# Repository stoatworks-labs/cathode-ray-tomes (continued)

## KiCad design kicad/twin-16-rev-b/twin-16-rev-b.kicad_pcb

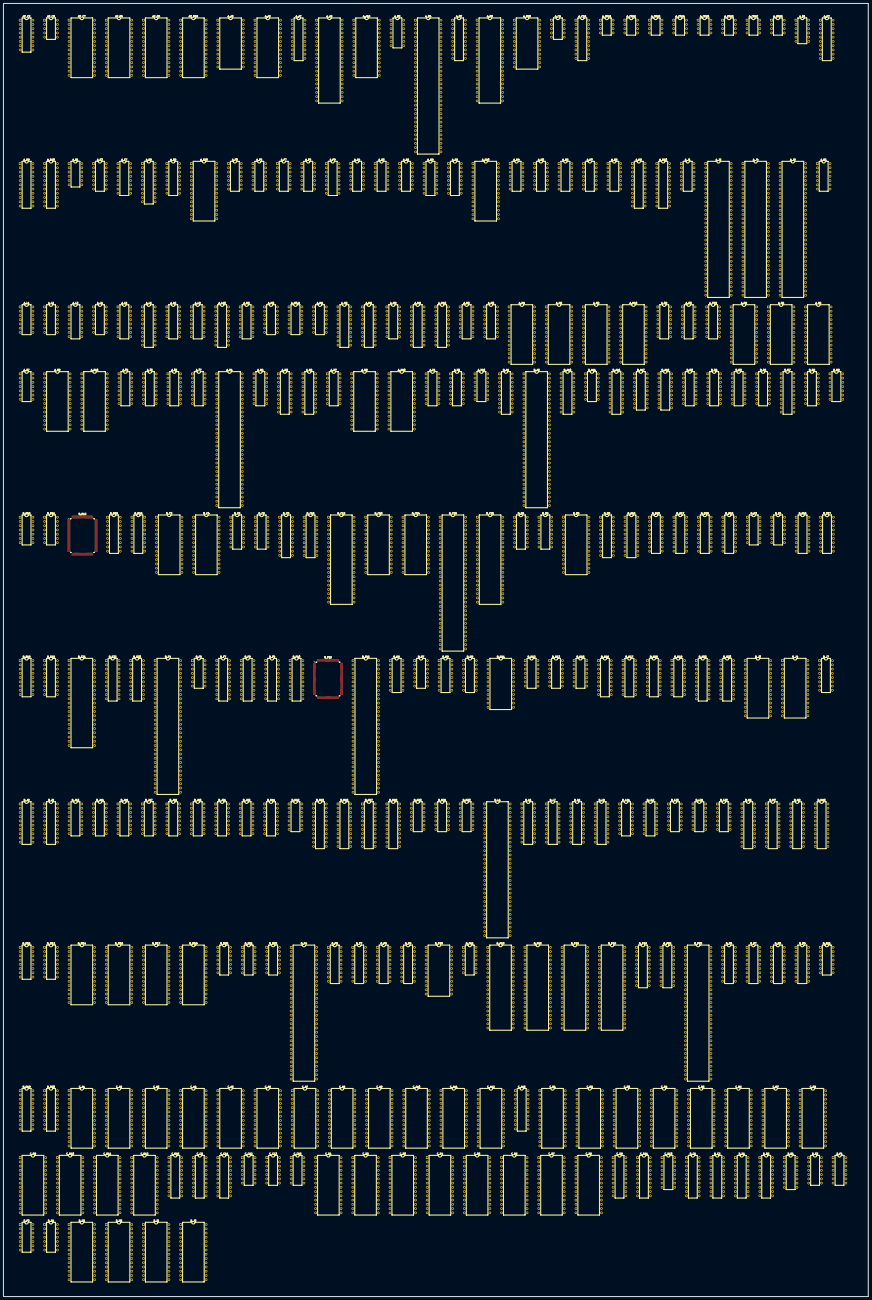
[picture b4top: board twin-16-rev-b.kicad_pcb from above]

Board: 2 copper layers, 517.2 x 773.3 mm, 297 parts (0 on the bottom side), 1272 nets, no tracks yet.

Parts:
AP_C2: YM3012; DIP-16_W7.62mm
AP_C5: 007340; DIP-10_W7.62mm
AP_C7: 23C1000; DIP-28_W15.24mm
AP_R4, AP_R6, AP_R10: 27C512; DIP-28_W15.24mm
A_A3: YM2151; DIP-24_W15.24mm
A_A5: 23C1000; DIP-28_W15.24mm
A_A7: 74LS273; DIP-20_W7.62mm
A_A8: Z80CPU; DIP-40_W15.24mm
A_A10: 27C256; DIP-28_W15.24mm
A_B2: uPC324; DIP-14_W7.62mm
A_B4: 007232; DIP-64_W15.24mm
A_B7: 74LS273; DIP-20_W7.62mm
A_B8: μPD7759; DIP-40_W15.24mm
A_B10: 2128SL; DIP-24_W15.24mm
A_C4: 007340; DIP-10_W7.62mm
A_C10: 74LS374; DIP-20_W7.62mm
A_CRA1, A_CRA2, A_CRA3, A_CRA4, A_CRA5, A_CRA6, A_CRA7, A_CRA8: 005273; DIP-8_W7.62mm
A_D1: MB3722; DIP-12_W7.62mm
A_D7: 74LS273; DIP-20_W7.62mm
A_D9, A_D10: 007644; DIP-22_W7.62mm
A_E1: 005924; DIP-12_W7.62mm
A_E3: uPC324; DIP-14_W7.62mm
A_E7: 74LS138; DIP-16_W7.62mm
A_E8: PAL16L8’; DIP-20_W7.62mm
A_E9: 74LS157; DIP-16_W7.62mm
A_E10: 6264SL; DIP-28_W15.24mm
A_F3: uPC324; DIP-14_W7.62mm
A_F6, A_F8: 74LS74; DIP-14_W7.62mm
A_F7: 74LS04; DIP-14_W7.62mm
A_F9: 74LS157; DIP-16_W7.62mm
A_G4: uPC324; DIP-14_W7.62mm
A_G5: 74LS74; DIP-14_W7.62mm
A_G6: 74LS00; DIP-14_W7.62mm
A_G8, A_G9: 74LS157; DIP-16_W7.62mm
A_G10: 6264SL; DIP-28_W15.24mm
A_H4: 74LS08; DIP-14_W7.62mm
A_H5, A_H6: 74LS74; DIP-14_W7.62mm
A_H7: 74LS04; DIP-14_W7.62mm
A_H8: 74LS07; DIP-14_W7.62mm
A_H9, A_H10: 007644; DIP-22_W7.62mm
A_J1: 74LS32; DIP-14_W7.62mm
A_J2: 007791; DIP-64_W15.24mm
A_J4, A_J8: 68000; DIP-64_W15.24mm
A_K1: 74LS32; DIP-14_W7.62mm
A_L1: 74LS07; DIP-14_W7.62mm
A_L2: 74LS00; DIP-14_W7.62mm
A_L3: 74LS138; DIP-16_W7.62mm
A_L4: 74LS74; DIP-14_W7.62mm
A_L5, A_L9: 74LS367; DIP-16_W7.62mm
A_L6, A_L10: 74LS244; DIP-20_W7.62mm
A_L8: 74HC367; DIP-16_W7.62mm
A_M2: 74LS253; DIP-16_W7.62mm
A_M3: 74LS74; DIP-14_W7.62mm
A_M3.4: 74LS02; DIP-14_W7.62mm
A_M4: 74LS21; DIP-14_W7.62mm
A_M5, A_M6, A_M9, A_M10: 74LS245; DIP-20_W7.62mm
A_M8: 74LS138; DIP-16_W7.62mm
A_N2: 74LS253; DIP-16_W7.62mm
A_N3: 74LS139; DIP-16_W7.62mm
A_N4, A_N6, A_N8, A_N10: 27C512; DIP-28_W15.24mm
A_O2: 74LS253; DIP-16_W7.62mm
A_O3: 74LS257; DIP-16_W7.62mm
A_PP2: 74LS253; DIP-16_W7.62mm
A_R8: 27C512; DIP-28_W15.24mm
A_S4, A_S6: 6264SL; DIP-28_W15.24mm
A_S7: 74LS30; DIP-14_W7.62mm
A_S8, A_S10: 27C512; DIP-28_W15.24mm
A_T4: 74LS257; DIP-16_W7.62mm
A_T5, A_T7: 74LS138; DIP-16_W7.62mm
A_T6: 74LS157; DIP-16_W7.62mm
A_U1: 007593; DIP-64_W15.24mm
A_U4: 74LS367; DIP-16_W7.62mm
A_U5, A_U6: 74LS273; DIP-20_W7.62mm
A_U7: 74LS174; DIP-16_W7.62mm
A_U8, A_U10: 6264SL; DIP-28_W15.24mm
A_V1, A_V2: 74LS157; DIP-16_W7.62mm
A_V10: 74LS74; DIP-14_W7.62mm
B_A4, B_A10: 74LS244; DIP-20_W7.62mm
B_A5: 007782; DIP-64_W15.24mm
B_A11: 74LS86; DIP-14_W7.62mm
B_A16: PAL16L8’; DIP-20_W7.62mm
B_A17, B_A19: 4464; DIP-18_W7.62mm
B_B3, B_B4, B_B5, B_B6, B_B8: 74LS157; DIP-16_W7.62mm
B_B7: 74LS273; DIP-20_W7.62mm
B_B9: 74LS04; DIP-14_W7.62mm
B_B10, B_B11: 74LS86; DIP-14_W7.62mm
B_B12: 007783; PQFP-100_14x20mm_P0.65mm
B_B16, B_B19: 4464; DIP-18_W7.62mm
B_C3, B_C4, B_C13, B_C14: 6264SL; DIP-28_W15.24mm
B_C5, B_C6: 74LS174; DIP-16_W7.62mm
B_C9, B_C10: 74LS273; DIP-20_W7.62mm
B_C12: 007784; DIP-42_W15.24mm
B_C16: 007786; DIP-64_W15.24mm
B_C21: 007787; DIP-42_W15.24mm
B_D5, B_D6: 74LS174; DIP-16_W7.62mm
B_D8: 27C128; DIP-28_W15.24mm
B_D9, B_D10: 74LS273; DIP-20_W7.62mm
B_D16, B_D17, B_D18, B_D19: 4464; DIP-18_W7.62mm
B_E3, B_E4: 74LS27; DIP-14_W7.62mm
B_E16, B_E17, B_E18, B_E19: 4464; DIP-18_W7.62mm
B_E21: 007787; DIP-42_W15.24mm
B_E22, B_E23: 74LS244; DIP-20_W7.62mm
B_F4: 007779; DIP-64_W15.24mm
B_F6: 74LS32; DIP-14_W7.62mm
B_F7, B_F8, B_F9, B_F10: 74LS245; DIP-20_W7.62mm
B_F12: 007785; PQFP-100_14x20mm_P0.65mm
B_F16: 007786; DIP-64_W15.24mm
B_H6: 74LS138; DIP-16_W7.62mm
B_H7: 74LS02; DIP-14_W7.62mm
B_H8, B_H9: 74LS174; DIP-16_W7.62mm
B_H11: GAL22V10; DIP-24_W15.24mm
B_H12: 74LS32; DIP-14_W7.62mm
B_H13: 74LS04; DIP-14_W7.62mm
B_H15: 74LS00; DIP-14_W7.62mm
B_H16, B_H17, B_H18, B_H19: 4464; DIP-18_W7.62mm
B_H22, B_H23: 74LS244; DIP-20_W7.62mm
B_J3, B_J4: 6264SL; DIP-28_W15.24mm
B_J7: 74LS153; DIP-16_W7.62mm
B_J8, B_J9: 74LS245; DIP-20_W7.62mm
B_J13, B_J14, B_J16, B_J17, B_J18, B_J20, B_J21, B_J23: 74LS157; DIP-16_W7.62mm
B_K11: 74LS153; DIP-16_W7.62mm
B_K12, B_K21, B_K23: 74LS32; DIP-14_W7.62mm
B_K13, B_K15, B_K17, B_K18: 007644; DIP-22_W7.62mm
B_K20: 74LS20; DIP-14_W7.62mm
B_L4: 007780; DIP-64_W15.24mm
B_L6, B_L7, B_L8, B_L9: 74LS245; DIP-20_W7.62mm
B_L11, B_L12: 74LS153; DIP-16_W7.62mm
B_L20: 74LS02; DIP-14_W7.62mm
B_L21, B_L23: 74LS32; DIP-14_W7.62mm
B_M6, B_M7, B_M8, B_M10: 007644; DIP-22_W7.62mm
B_M11, B_M12: 74LS153; DIP-16_W7.62mm
B_M14, B_M15, B_M17, B_M19: SRAM32K8B; DIP-28_W15.24mm
B_N20: 74LS02; DIP-14_W7.62mm
B_N21, B_N23: 74LS32; DIP-14_W7.62mm
B_P4: 007781; DIP-64_W15.24mm
B_P6, B_P7, B_P8, B_P9: 4464; DIP-18_W7.62mm
B_P10: GAL22V10; DIP-24_W15.24mm
B_P11: 74LS74; DIP-14_W7.62mm
B_P13, B_P15, B_P16, B_P18: 23C4100; DIP-40_W15.24mm
B_P19, B_P20: 74LS374; DIP-20_W7.62mm
B_P23: 007786; DIP-64_W15.24mm
B_R6, B_R7, B_R8, B_R9: 4464; DIP-18_W7.62mm
B_R11: 74LS32; DIP-14_W7.62mm
B_R19, B_R20: 74LS374; DIP-20_W7.62mm
C_A1, C_A2, C_A3, C_A4, C_A5, C_A6, C_A7, C_A8, C_A9, C_A10, C_A11, C_A12: 27C512; DIP-28_W15.24mm
C_A15: 74LS244; DIP-20_W7.62mm
C_B1, C_B2, C_B3, C_B4, C_B5, C_B6, C_B7, C_B8, C_B9, C_B10, C_B11, C_B12: 27C512; DIP-28_W15.24mm
C_B15: 74LS244; DIP-20_W7.62mm
C_C9, C_C11: 74LS244; DIP-20_W7.62mm
C_C12: 74LS08; DIP-14_W7.62mm
C_C13: 74LS04; DIP-14_W7.62mm
C_C15: 74LS32; DIP-14_W7.62mm
C_D1, C_D2, C_D3, C_D4, C_D5, C_D6, C_D7, C_D8: 27C512; DIP-28_W15.24mm
C_D9, C_D11: 74LS244; DIP-20_W7.62mm
C_D13: 74LS138; DIP-16_W7.62mm
D_C1, D_C2: 74LS245; DIP-20_W7.62mm
D_D1, D_D2: 74LS245; DIP-20_W7.62mm
D_E1: 74LS174; DIP-16_W7.62mm
D_E2: 74LS32; DIP-14_W7.62mm
D_F1: 74LS04; DIP-14_W7.62mm
D_F2: 74LS32; DIP-14_W7.62mm
D_G1: 74LS32; DIP-14_W7.62mm
D_G2: 6264SL; DIP-28_W15.24mm
D_H2: 6264SL; DIP-28_W15.24mm
D_I2: 6264SL; DIP-28_W15.24mm
D_J2: 6264SL; DIP-28_W15.24mm

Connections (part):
+12V: A_D1.10, A_E1.11, A_E3.4, A_F3.4
/1C0: B_K12.10, B_M12.5, B_P4.50
/1C1: B_K12.9, B_M12.11, B_P4.49
/1C2: B_K12.13, B_L12.5, B_P4.31
/1C3: B_K12.12, B_L12.11, B_P4.30
/1C4: B_M11.5, B_P4.29
/1C5: B_M11.11, B_P4.2
/1C6: B_K11.5, B_P4.1, B_P10.11
/1V: B_A5.50, B_C6.3, B_F4.1
/2C0: B_M12.6, B_P4.57, B_P10.4
/2C1: B_M12.10, B_P4.56, B_P10.17
/2C2: B_L12.6, B_P4.55, B_P10.18
/2C3: B_L12.10, B_P4.54, B_P10.19
/2C4: B_M11.6, B_P4.53
/2C5: B_M11.10, B_P4.52
/2V: B_A5.51, B_C6.4
/4V: B_A5.52, B_C6.6
/8H: B_A5.46, B_A16.4, B_B6.6
/8V: B_A5.53, B_B5.13
/16H: B_A5.45, B_B6.10
/16V: B_A5.54, B_B4.3
/32H: B_A5.44, B_B6.13
/32V: B_A5.55, B_B4.6
/64H: B_A5.43, B_B5.3
/64V: B_A5.56, B_B4.10
/128H: B_A5.42, B_B5.6
/128V: B_A5.57, B_B4.13
/256H: B_A5.41, B_B5.10
/AB1: AP_R4.10, AP_R6.10, A_E9.14, A_F7.3, A_L6.18, A_M2.14, A_N2.14, A_N4.10, A_N6.10, A_O2.14, A_O3.1, A_PP2.14, A_S4.10, A_S6.10, A_T4.1, A_U1.44, B_B6.5, B_B12.16, B_F4.25, B_H6.1, D_C2.2
/AB2: AP_R4.9, AP_R6.9, A_G9.2, A_L6.16, A_M2.2, A_N2.2, A_N4.9, A_N6.9, A_O2.2, A_PP2.2, A_S4.9, A_S6.9, A_V1.5, B_B6.11, B_B12.15, B_F4.24, B_H6.2, D_C2.3
/AB3: AP_R4.8, AP_R6.8, A_G9.5, A_L6.14, A_N4.8, A_N6.8, A_S4.8, A_S6.8, A_T5.1, A_V1.11, B_B6.14, B_B12.14, B_F4.23, B_H6.3, D_C2.4
/AB4: AP_R4.7, AP_R6.7, A_G9.11, A_L6.12, A_N4.7, A_N6.7, A_S4.7, A_S6.7, A_T5.2, A_V1.14, B_B5.2, B_B12.13, B_F4.22, D_C2.5
/AB5: AP_R4.6, AP_R6.6, A_G9.14, A_L6.9, A_N4.6, A_N6.6, A_S4.6, A_S6.6, A_V2.2, B_B5.5, B_B12.12, B_F4.21, D_C2.6
/AB6: AP_R4.5, AP_R6.5, A_G8.2, A_L6.7, A_N4.5, A_N6.5, A_S4.5, A_S6.5, A_V2.5, B_B5.11, B_B12.11, B_F4.20, D_C2.7
/AB7: AP_R4.4, AP_R6.4, A_G8.5, A_L6.5, A_N4.4, A_N6.4, A_S4.4, A_S6.4, A_V2.11, B_B5.14, B_B12.10, B_F4.19, D_C2.8
/AB8: AP_R4.3, AP_R6.3, A_G8.11, A_L6.3, A_N4.3, A_N6.3, A_S4.3, A_S6.3, A_V2.14, B_B4.2, B_B12.9, B_F4.18, D_C2.9
/AB9: AP_R4.25, AP_R6.25, A_G8.14, A_L5.3, A_N4.25, A_N6.25, A_S4.25, A_S6.25, A_T6.2, B_B4.5, B_B12.8, B_F4.17, D_D2.2
/AB10: AP_R4.24, AP_R6.24, A_F9.2, A_L5.5, A_N4.24, A_N6.24, A_S4.24, A_S6.24, A_T6.5, B_B4.11, B_B12.7, B_F4.15, D_D2.3
/AB11: AP_R4.21, AP_R6.21, A_F9.5, A_L5.7, A_N4.21, A_N6.21, A_S4.21, A_S6.21, A_T6.11, B_B4.14, B_B12.6, B_F4.14
/AB12: AP_R4.23, AP_R6.23, A_F9.11, A_L5.9, A_N4.23, A_N6.23, A_S4.23, A_S6.23, A_T6.14, B_B3.2, B_B12.5, B_F4.13
/AB13: AP_R4.2, AP_R6.2, A_F9.14, A_L5.11, A_N4.2, A_N6.2, A_S4.2, A_S6.2, B_B3.5, B_B12.4, B_J7.12
/BUS: B_K11.6, B_P4.51, B_P10.13
/Battery Powered RAM/AB'1: D_C2.18, D_G2.10, D_H2.10, D_I2.10, D_J2.10
/Battery Powered RAM/AB'2: D_C2.17, D_G2.9, D_H2.9, D_I2.9, D_J2.9
/Battery Powered RAM/AB'3: D_C2.16, D_G2.8, D_H2.8, D_I2.8, D_J2.8
/Battery Powered RAM/AB'4: D_C2.15, D_G2.7, D_H2.7, D_I2.7, D_J2.7
/Battery Powered RAM/AB'5: D_C2.14, D_G2.6, D_H2.6, D_I2.6, D_J2.6
/Battery Powered RAM/AB'6: D_C2.13, D_G2.5, D_H2.5, D_I2.5, D_J2.5
/Battery Powered RAM/AB'7: D_C2.12, D_G2.4, D_H2.4, D_I2.4, D_J2.4
/Battery Powered RAM/AB'8: D_C2.11, D_G2.3, D_H2.3, D_I2.3, D_J2.3
/Battery Powered RAM/AB'9: D_D2.18, D_G2.25, D_H2.25, D_I2.25, D_J2.25
/Battery Powered RAM/AB'10: D_D2.17, D_F1.3, D_G1.10
/Battery Powered RAM/DB'0: D_C1.18, D_G2.11, D_H2.11
/Battery Powered RAM/DB'1: D_C1.17, D_G2.12, D_H2.12
/Battery Powered RAM/DB'2: D_C1.16, D_G2.13, D_H2.13
/Battery Powered RAM/DB'3: D_C1.15, D_G2.15, D_H2.15
/Battery Powered RAM/DB'4: D_C1.14, D_G2.16, D_H2.16
/Battery Powered RAM/DB'5: D_C1.13, D_G2.17, D_H2.17
/Battery Powered RAM/DB'6: D_C1.12, D_G2.18, D_H2.18
/Battery Powered RAM/DB'7: D_C1.11, D_G2.19, D_H2.19
/Battery Powered RAM/DB'8: D_D1.18, D_E1.3, D_I2.11, D_J2.11
/Battery Powered RAM/DB'9: D_D1.17, D_E1.4, D_I2.12, D_J2.12
/Battery Powered RAM/DB'10: D_D1.16, D_E1.6, D_I2.13, D_J2.13
/Battery Powered RAM/DB'11: D_D1.15, D_E1.11, D_I2.15, D_J2.15
/Battery Powered RAM/DB'12: D_D1.14, D_E1.13, D_I2.16, D_J2.16
/Battery Powered RAM/DB'13: D_D1.13, D_I2.17, D_J2.17
/Battery Powered RAM/DB'14: D_D1.12, D_I2.18, D_J2.18
/Battery Powered RAM/DB'15: D_D1.11, D_I2.19, D_J2.19
/Battery Powered RAM/DB''8: D_E1.2, D_G2.24, D_H2.24, D_I2.24, D_J2.24
/Battery Powered RAM/DB''9: D_E1.5, D_G2.21, D_H2.21, D_I2.21, D_J2.21
/Battery Powered RAM/DB''10: D_E1.7, D_G2.23, D_H2.23, D_I2.23, D_J2.23
/Battery Powered RAM/DB''11: D_E1.10, D_G2.2, D_H2.2, D_I2.2, D_J2.2
/Battery Powered RAM/DB''12: D_E1.12, D_E2.2, D_F1.5
/Battery Powered RAM/MA16': D_D2.13, D_F1.1
/Battery Powered RAM/~CPURES': D_D2.11, D_E1.1
/Battery Powered RAM/~HRAMEN: D_F2.1, D_F2.5, D_F2.10, D_F2.11
/Battery Powered RAM/~IOCS': D_D2.12, D_G1.4
/Battery Powered RAM/~LRAMEN: D_E2.3, D_E2.4, D_E2.10, D_E2.13
/Battery Powered RAM/~MLWR': D_D2.15, D_E2.12, D_F2.9
/Battery Powered RAM/~MREAD2': D_C1.1, D_D1.1, D_D2.16, D_E2.5, D_F2.2
/Battery Powered RAM/~MUWR': D_D2.14, D_E2.9, D_F2.4
/Battery Powered RAM/~RAMEN: D_G2.20, D_H2.20, D_I2.20, D_J2.20
/Battery Powered RAM/~RAM: D_C1.19, D_D1.19, D_G1.2, D_G1.6, D_G1.9
/Battery Powered RAM/~RWEN: D_E2.1, D_F2.12, D_G1.8
/CHAPAGE: A_G5.5, B_J13.14
/CLK2: A_U1.40, A_U6.11, A_U7.9, B_A10.12
/CLK21: B_A10.9, B_A16.8, B_B12.50, B_C9.11, B_C10.11, B_C12.42, B_C16.37, B_C21.14, B_D10.11, B_E21.14, B_F12.25, B_F16.37
/CLK22: B_A4.12, B_F4.5, B_L4.17, B_P4.46, B_P23.37
/CPUCLK: A_E8.16, A_G5.11, A_L8.6, B_A5.39
/Color mixer/1C: B_K12.6, B_P10.1
/Color mixer/CB0: A_U7.12, A_V1.6
/Color mixer/CB1: A_U7.15, A_V1.10
/Color mixer/CB2: A_U6.2, A_V1.13
/Color mixer/CB3: A_U6.5, A_V2.3
/Color mixer/CB4: A_U6.6, A_V2.6
/Color mixer/CB5: A_U6.9, A_V2.10
/Color mixer/CB6: A_U6.12, A_V2.13
/Color mixer/CO1: A_U1.46, A_V1.7
/Color mixer/CO2: A_U1.47, A_V1.9
/Color mixer/CO3: A_U1.48, A_V1.12
/Color mixer/CO4: A_U1.49, A_V2.4
/Color mixer/CO5: A_U1.50, A_V2.7
/Color mixer/CO6: A_U1.51, A_V2.9
/Color mixer/CO7: A_U1.52, A_V2.12
/Color mixer/CO8: A_T6.4, A_U1.53
/Color mixer/CO9: A_T6.7, A_U1.54
/Color mixer/CO10: A_T6.9, A_U1.55
/Color mixer/CO11: A_T6.12, A_U1.56
/Color mixer/COLOR0: A_U7.13, B_M12.7
/Color mixer/COLOR1: A_U7.14, B_M12.9
/Color mixer/COLOR2: A_U6.3, B_L12.7
/Color mixer/COLOR3: A_U6.4, B_L12.9
/Color mixer/COLOR4: A_U6.7, B_M11.7
/Color mixer/COLOR5: A_U6.8, B_M11.9
/Color mixer/COLOR6: A_U6.13, B_K11.7
/Color mixer/COLOR7: A_U6.14, B_K11.9
/Color mixer/COLOR8: A_U6.17, B_L11.7
/Color mixer/COLOR9: A_U6.18, B_L11.9
/Color mixer/FX: B_P10.10, B_R11.6
/Color mixer/SELA: B_K11.14, B_L11.14, B_L12.14, B_M11.14, B_M12.14, B_P10.20
/Color mixer/SELB: B_K11.2, B_L11.2, B_L12.2, B_M11.2, B_M12.2, B_P10.21
/Color mixer/SHADOW: A_U7.6, B_P10.23
/Color mixer/~CBLK': A_U1.39, A_U7.5
/Color mixer/~COE: A_U1.9, A_V1.4
/DB0: AP_R4.11, A_C10.3, A_D10.13, A_M2.9, A_M5.18, A_N4.11, A_S4.11, A_T4.4, A_U1.21, A_U4.9, A_U5.3, B_A5.36, B_C12.22, B_D9.3, B_F4.26, B_F8.9, B_F9.2, B_H8.3, B_H9.3, B_L7.2, D_C1.2
/DB1: AP_R4.12, A_C10.4, A_D10.14, A_M2.7, A_M5.17, A_N4.12, A_S4.12, A_T4.7, A_U1.22, A_U4.7, A_U5.4, B_C12.23, B_D9.4, B_F4.27, B_F8.8, B_F9.3, B_H8.4, B_H9.4, B_L7.3, D_C1.3
/DB2: AP_R4.13, A_C10.7, A_D10.15, A_M5.16, A_N2.9, A_N4.13, A_S4.13, A_T4.12, A_U1.23, A_U4.5, A_U5.7, B_C12.24, B_D9.7, B_F4.28, B_F8.7, B_F9.4, B_H8.6, B_H9.6, B_L7.4, D_C1.4
/DB3: AP_R4.15, A_C10.8, A_D10.16, A_M5.15, A_N2.7, A_N4.15, A_S4.15, A_T4.9, A_U1.24, A_U4.3, A_U5.8, B_C12.25, B_D9.8, B_F4.29, B_F8.6, B_F9.5, B_L7.5, D_C1.5
/DB4: AP_R4.16, A_C10.13, A_D10.17, A_M5.14, A_N4.16, A_O2.9, A_O3.4, A_S4.16, A_U1.25, A_U5.13, B_C12.26, B_D9.13, B_F4.30, B_F8.5, B_F9.6, B_L7.6, D_C1.6
/DB5: AP_R4.17, A_C10.14, A_D10.18, A_M5.13, A_N4.17, A_O2.7, A_O3.7, A_S4.17, A_U1.26, A_U5.14, B_C12.27, B_D9.14, B_F4.31, B_F8.4, B_F9.7, B_L7.7, D_C1.7
/DB6: AP_R4.18, A_C10.17, A_D10.19, A_M5.12, A_N4.18, A_O3.12, A_PP2.7, A_S4.18, A_U1.27, A_U5.17, B_C12.28, B_D9.17, B_F4.33, B_F8.3, B_F9.8, B_L7.8, D_C1.8
/DB7: AP_R4.19, A_C10.18, A_D10.20, A_M5.11, A_N4.19, A_O3.9, A_PP2.9, A_S4.19, A_U1.28, A_U5.18, B_C12.29, B_D9.18, B_F4.34, B_F8.2, B_F9.9, B_L7.9, D_C1.9
/DB8: AP_R6.11, A_H9.13, A_M6.18, A_N6.11, A_S6.11, B_C12.30, B_F4.35, B_F7.9, B_F10.2, B_L6.2, D_D1.2
/DB9: AP_R6.12, A_H9.14, A_M6.17, A_N6.12, A_S6.12, B_C12.31, B_F7.8, B_F10.3, B_L6.3, D_D1.3
/DB10: AP_R6.13, A_H9.15, A_M6.16, A_N6.13, A_S6.13, B_C12.33, B_F7.7, B_F10.4, B_L6.4, D_D1.4
/DB11: AP_R6.15, A_H9.16, A_M6.15, A_N6.15, A_S6.15, B_C12.34, B_F7.6, B_F10.5, B_L6.5, D_D1.5
/DB12: AP_R6.16, A_H9.17, A_M6.14, A_N6.16, A_S6.16, B_C12.35, B_F7.5, B_F10.6, B_L6.6, D_D1.6
/DB13: AP_R6.17, A_H9.18, A_M6.13, A_N6.17, A_S6.17, B_C12.36, B_F7.4, B_F10.7, B_L6.7, D_D1.7
/DB14: AP_R6.18, A_H9.19, A_M6.12, A_N6.18, A_S6.18, B_C12.37, B_F7.3, B_F10.8, B_L6.8, D_D1.8
/DB15: AP_R6.19, A_H9.20, A_M6.11, A_N6.19, A_S6.19, B_C12.38, B_F7.2, B_F10.9, B_L6.9, D_D1.9
/DMA: B_A5.4, B_A16.2, B_B12.36, B_C12.3
/DMAINIT: A_M3.4.2, A_M3.4.12, B_A5.6, B_A16.11, B_F12.77, B_H12.1, B_K12.2
/DMAON: A_U5.16, B_B12.2, B_P11.2
/FBREF: B_A4.3, B_B12.53, B_F12.76
/FX0: B_D10.2, B_M12.3, B_R11.10
/FX1: B_D10.5, B_M12.13, B_R11.9
/FX2: B_D10.6, B_L12.3, B_R11.12
/FX3: B_D10.9, B_L12.13, B_R11.13
/FX4: B_D10.12, B_M11.3
/FX5: B_D10.15, B_M11.13
/FX6: B_D10.16, B_K11.3
/FX7: B_D10.19, B_K11.13
/Fixed Layer/A0: B_B6.7, B_C3.10, B_C4.10
/Fixed Layer/A1: B_B6.9, B_C3.9, B_C4.9
/Fixed Layer/A2: B_B6.12, B_C3.8, B_C4.8
/Fixed Layer/A3: B_B5.4, B_C3.7, B_C4.7
/Fixed Layer/A4: B_B5.7, B_C3.6, B_C4.6
/Fixed Layer/A5: B_B5.9, B_C3.5, B_C4.5
/Fixed Layer/A6: B_B5.12, B_C3.4, B_C4.4
/Fixed Layer/A7: B_B4.4, B_C3.3, B_C4.3
/Fixed Layer/A8: B_B4.7, B_C3.25, B_C4.25
/Fixed Layer/A9: B_B4.9, B_C3.24, B_C4.24
/Fixed Layer/A10: B_B4.12, B_C3.21, B_C4.21
/Fixed Layer/A11: B_B3.4, B_C3.23, B_C4.23
/Fixed Layer/A12: B_B3.7, B_C3.2, B_C4.2
/Fixed Layer/D0: B_C4.11, B_C6.11, B_F8.11
/Fixed Layer/D1: B_C4.12, B_C6.13, B_F8.12
/Fixed Layer/D2: B_C4.13, B_C6.14, B_F8.13
/Fixed Layer/D3: B_C4.15, B_D6.3, B_F8.14
/Fixed Layer/D4: B_C4.16, B_D6.4, B_F8.15
/Fixed Layer/D5: B_C4.17, B_D6.6, B_F8.16
/Fixed Layer/D6: B_C4.18, B_D6.11, B_F8.17
/Fixed Layer/D7: B_C4.19, B_D6.13, B_F8.18
/Fixed Layer/D8: B_C3.11, B_D6.14, B_F7.11
/Fixed Layer/D9: B_C3.12, B_D5.3, B_F7.12
/Fixed Layer/D10: B_C3.13, B_D5.4, B_F7.13
/Fixed Layer/D11: B_C3.15, B_D5.6, B_F7.14
/Fixed Layer/D12: B_C3.16, B_D5.11, B_F7.15
/Fixed Layer/D13: B_C3.17, B_D5.13, B_F7.16
/Fixed Layer/D14: B_C3.18, B_D5.14, B_F7.17
/Fixed Layer/D15: B_C3.19, B_F7.18
/Fixed Layer/FX10: B_B7.12, B_B8.2
/Fixed Layer/FX11: B_B7.15, B_B8.5
/Fixed Layer/FX12: B_B7.16, B_B8.11
/Fixed Layer/FX13: B_B7.19, B_B8.14
/Fixed Layer/FX20: B_B7.2, B_B8.3
/Fixed Layer/FX21: B_B7.5, B_B8.6
/Fixed Layer/FX22: B_B7.6, B_B8.10
/Fixed Layer/FX23: B_B7.9, B_B8.13
/Fixed Layer/~OE: B_B6.4, B_C3.22, B_C4.22
/Fixed Layer/~P1HB: B_A11.8, B_B7.11, B_C5.9
/Fixed Layer/~P4H: B_A11.3, B_C6.9, B_D5.9, B_D6.9
/HFLIP: B_A5.30, B_A11.5, B_A11.13, B_A16.5, B_B11.2, B_C16.35, B_C21.16, B_D9.5, B_E21.16, B_F16.35, B_P4.45
/IO/COIN1: A_CRA2.8, A_U5.2
/IO/COIN2: A_CRA8.8, A_E1.6, A_U5.5
/IO/COIN3: A_CRA3.8, A_U5.6
/IO/SOUND-ON: A_H5.11, A_U5.9
/IO/Y3: A_CRA1.5, A_PP2.5
/IO/Y4: A_CRA1.7, A_PP2.6
/IO/Y5: A_CRA4.1, A_PP2.13
/IO/Y6: A_CRA4.3, A_PP2.12
/IO/Y7: A_CRA4.5, A_PP2.11
/IO/Y8: A_CRA4.7, A_PP2.10
/IO/Y9: A_CRA5.1, A_O2.3
/IO/Y10: A_CRA5.3, A_O2.4
/IO/Y11: A_CRA5.5, A_O2.5
/IO/Y12: A_CRA5.7, A_O2.6
/IO/Y13: A_CRA6.1, A_O2.13
/IO/Y14: A_CRA6.3, A_O2.12
/IO/Y15: A_CRA6.5, A_O2.11
/IO/Y16: A_CRA6.7, A_O2.10
/IO/Y17: A_CRA7.1, A_N2.3
/IO/Y18: A_CRA7.3, A_N2.4
/IO/Y19: A_CRA7.5, A_N2.5
/IO/Y20: A_CRA7.7, A_N2.6
/IO/Y21: A_CRA3.1, A_N2.13
/IO/Y22: A_CRA3.3, A_N2.12
/IO/Y23: A_CRA3.5, A_N2.11
/IO/Y24: A_CRA3.7, A_N2.10
/IO/Y25: A_CRA8.1, A_M2.3
/IO/Y26: A_CRA8.3, A_M2.4
/IO/Y27: A_CRA8.5, A_M2.5
/IO/Y28: A_CRA8.7, A_M2.6
/IO/Y29: A_CRA2.1, A_M2.13
/IO/Y30: A_CRA2.3, A_M2.12
/IO/Y31: A_CRA2.5, A_M2.11
/IO/Y32: A_CRA2.7, A_M2.10
/IO/~AFR: A_E1.2, A_T5.13
/IO/~SHOOT: A_M2.1, A_M2.15, A_N2.1, A_N2.15, A_O2.1, A_O2.15, A_PP2.1, A_PP2.15, A_T5.11
/IO/~SOUND-DATA: A_C10.11, A_T5.14
/IO/~WDRES: A_E1.4, A_L8.2
/MINT16EN: A_M3.10, A_U5.15
/Main CPU/AB14: AP_R4.26, AP_R6.26, A_L5.13, A_N4.26, A_N6.26
/Main CPU/BUSE: A_H7.1, A_J2.5
/Main CPU/CLK: A_J2.18, A_J4.15, A_L8.9
/Main CPU/MA1: A_J2.4, A_J4.29, A_L6.2
/Main CPU/MA2: A_J2.3, A_J4.30, A_L6.4
/Main CPU/MA3: A_J2.2, A_J4.31, A_L6.6
/Main CPU/MA4: A_J4.32, A_L6.8
/Main CPU/MA5: A_J2.63, A_J4.33, A_L6.11
/Main CPU/MA6: A_J2.62, A_J4.34, A_L6.13
/Main CPU/MA7: A_J2.61, A_J4.35, A_L6.15
/Main CPU/MA8: A_J2.60, A_J4.36, A_L6.17
/Main CPU/MA9: A_J2.59, A_J4.37, A_L5.2
/Main CPU/MA10: A_J2.58, A_J4.38, A_L5.4
/Main CPU/MA11: A_J2.57, A_J4.39, A_L5.6
/Main CPU/MA12: A_J2.56, A_J4.40, A_L5.10
/Main CPU/MA13: A_J2.55, A_J4.41, A_L5.12
/Main CPU/MA14: A_J2.54, A_J4.42, A_L5.14
/Main CPU/MA15: AP_R4.27, AP_R6.27, A_J2.53, A_J4.43, A_N4.27, A_N6.27
/Main CPU/MA16: AP_R4.1, AP_R6.1, A_J2.52, A_J4.44, A_N4.1, A_N6.1, A_T5.4, D_D2.7
/Main CPU/MA17: A_J2.51, A_J4.45, A_L3.1, A_N3.2
/Main CPU/MA18: A_J2.50, A_J4.46, A_L3.2, A_N3.3
/Main CPU/MA19: A_J2.49, A_J4.47, A_L3.3
/Main CPU/MA20: A_J2.47, A_J4.48, A_K1.2, A_L2.5, A_L3.4
/Main CPU/MA21: A_J2.46, A_J4.50
/Main CPU/MA22: A_J2.45, A_J4.51
/Main CPU/MA23: A_G6.1, A_J2.44, A_J4.52
/Main CPU/MAS: A_G6.2, A_H7.12, A_L2.4
/Main CPU/MD0: A_J2.27, A_J4.5, A_M5.2
/Main CPU/MD1: A_J2.28, A_J4.4, A_M5.3
/Main CPU/MD2: A_J2.29, A_J4.3, A_M5.4
/Main CPU/MD3: A_J2.30, A_J4.2, A_M5.5
/Main CPU/MD4: A_J2.31, A_J4.1, A_M5.6
/Main CPU/MD5: A_J2.33, A_J4.64, A_M5.7
/Main CPU/MD6: A_J2.34, A_J4.63, A_M5.8
/Main CPU/MD7: A_J2.35, A_J4.62, A_M5.9
/Main CPU/MD8: A_J2.36, A_J4.61, A_M6.2
/Main CPU/MD9: A_J2.37, A_J4.60, A_M6.3
/Main CPU/MD10: A_J2.38, A_J4.59, A_M6.4
/Main CPU/MD11: A_J2.39, A_J4.58, A_M6.5
/Main CPU/MD12: A_J2.40, A_J4.57, A_M6.6
/Main CPU/MD13: A_J2.41, A_J4.56, A_M6.7
/Main CPU/MD14: A_J2.42, A_J4.55, A_M6.8
/Main CPU/MD15: A_J2.43, A_J4.54, A_M6.9
/Main CPU/~BERR: A_J2.1, A_J4.22
/Main CPU/~BGACK: A_J2.20, A_J4.12
/Main CPU/~BG: A_J2.21, A_J4.11
/Main CPU/~BR: A_J2.19, A_J4.13
/Main CPU/~DTACK: A_J2.22, A_J4.10, A_L1.2
/Main CPU/~HALT: A_J2.17, A_J4.17, A_L1.8
/Main CPU/~IPL0: A_J2.8, A_J4.25, A_L2.8
/Main CPU/~IPL1: A_H4.1, A_J2.9, A_J4.24, A_L2.9, A_M3.5
/Main CPU/~IPL2: A_H4.3, A_J2.10, A_J4.23
/Main CPU/~LDS: A_J2.24, A_J4.8, A_K1.12
/Main CPU/~MAS: A_H7.13, A_J2.26, A_J4.6, A_K1.1, A_L3.5
/Main CPU/~MWORKCS: A_L3.12, A_S4.20, A_S6.20
/Main CPU/~RESET: A_J2.15, A_J4.18, A_L1.10
/Main CPU/~UDS: A_J1.4, A_J2.25, A_J4.7
/N2H: B_H12.5, B_H13.8, B_K13.12, B_K15.12, B_K17.12, B_K18.12, B_P19.11, B_P20.11, B_R19.11, B_R20.11
/OBJBUFINIT: B_A5.5, B_A16.7, B_B12.55, B_C12.2, B_P11.3
/OCD0: B_E21.21, B_M12.4, B_P10.6
/OCD1: B_E21.20, B_M12.12, B_P10.7
/OCD2: B_E21.19, B_L12.4, B_P10.8
/OCD3: B_E21.18, B_L12.12, B_P10.9
/OCD4: B_C21.21, B_M11.4
/OCD5: B_C21.20, B_M11.12
/OCD6: B_C21.19, B_K11.4
/OCD7: B_C21.18, B_K11.12
/P1H: B_A4.6, B_A5.47, B_A16.3
/P1HB: B_A4.14, B_A11.10, B_A11.12, B_F4.4, B_F12.46, B_L4.23
/P2H: B_A5.17, B_B3.1, B_B4.1, B_B5.1, B_B6.1, B_B11.1, B_B11.4, B_E4.2, B_E4.4, B_F6.2, B_H7.3, B_H7.5, B_H11.1, B_H13.9, B_J7.14, B_J13.1, B_J14.1, B_J16.1, B_J17.1, B_J18.1, B_J20.3, B_J20.5
/P4H: B_A5.15, B_A11.2, B_A11.4, B_H11.2, B_J7.2
/P256VD: B_A5.23, B_C16.33, B_C21.17, B_E21.17, B_F12.53, B_H7.6, B_H15.2, B_J20.1, B_J21.1, B_J23.1, B_P23.33
/PI0: B_D9.6, B_P10.2
/PI1: B_D9.9, B_P10.3
/PI2: B_D9.12, B_P10.5
/R~W: A_H7.3, A_H7.11, A_J1.5, A_J2.23, A_J4.9, A_K1.13, A_T5.3
/SA15: AP_R10.27, A_J8.43, A_N8.27, A_N10.27, A_R8.27, A_S8.27, A_S10.27, B_J14.5, B_L4.55
/SA16: AP_R10.1, A_J8.44, A_N8.1, A_N10.1, A_R8.1, A_S8.1, A_S10.1, B_J14.11, B_L4.54
/SA17: A_J8.45, A_M8.1, B_J14.14, B_L4.53
/SA18: A_J8.46, A_M8.2, B_J13.2
/SA19: A_J8.47, A_M8.3, A_T7.1, B_J13.5
/SA20: A_J8.48, A_T7.2, B_J13.11
/SA21: A_J8.50, A_T7.3
/SA22: A_J8.51, A_K1.5, A_M8.4, A_T7.6
/SA23: A_G6.4, A_J8.52, A_T7.4
/SAB1: AP_R10.10, A_E9.13, A_L10.18, A_N8.10, A_N10.10, A_R8.10, A_S8.10, A_S10.10, A_U8.2, A_U10.10, B_B12.31, B_F4.36, B_H11.9, B_L4.6
/SAB2: AP_R10.9, A_G9.3, A_L10.16, A_N8.9, A_N10.9, A_R8.9, A_S8.9, A_S10.9, A_U8.23, A_U10.9, B_B12.30, B_F4.37, B_J17.2, B_L4.5
/SAB3: AP_R10.8, A_G9.6, A_L10.14, A_N8.8, A_N10.8, A_R8.8, A_S8.8, A_S10.8, A_U8.21, A_U10.8, B_B12.29, B_F4.38, B_J17.5, B_L4.4
/SAB4: AP_R10.7, A_G9.10, A_L10.12, A_N8.7, A_N10.7, A_R8.7, A_S8.7, A_S10.7, A_U8.24, A_U10.7, B_B12.28, B_F4.39, B_J17.11, B_L4.3
/SAB5: AP_R10.6, A_G9.13, A_L10.9, A_N8.6, A_N10.6, A_R8.6, A_S8.6, A_S10.6, A_U8.25, A_U10.6, B_B12.27, B_F4.40, B_J17.14, B_L4.2
/SAB6: AP_R10.5, A_G8.3, A_L10.7, A_N8.5, A_N10.5, A_R8.5, A_S8.5, A_S10.5, A_U8.3, A_U10.5, B_B12.26, B_F4.41, B_J16.2, B_L4.1
/SAB7: AP_R10.4, A_G8.6, A_L10.5, A_N8.4, A_N10.4, A_R8.4, A_S8.4, A_S10.4, A_U8.4, A_U10.4, B_B12.25, B_F4.42, B_J16.5, B_L4.63
/SAB8: AP_R10.3, A_G8.10, A_L10.3, A_N8.3, A_N10.3, A_R8.3, A_S8.3, A_S10.3, A_U8.5, A_U10.3, B_B12.24, B_F4.43, B_J16.11, B_L4.62
/SAB9: AP_R10.25, A_G8.13, A_L9.3, A_N8.25, A_N10.25, A_R8.25, A_S8.25, A_S10.25, A_U8.6, A_U10.25, B_B12.23, B_F4.44, B_J16.14, B_L4.61
/SAB10: AP_R10.24, A_F9.3, A_L9.5, A_N8.24, A_N10.24, A_R8.24, A_S8.24, A_S10.24, A_U8.7, A_U10.24, B_B12.20, B_F4.45, B_J18.2, B_L4.60
/SAB11: AP_R10.21, A_F9.6, A_L9.7, A_N8.21, A_N10.21, A_R8.21, A_S8.21, A_S10.21, A_U8.8, A_U10.21, B_B12.19, B_F4.59, B_J18.5, B_L4.59
/SAB12: AP_R10.23, A_F9.10, A_L9.9, A_N8.23, A_N10.23, A_R8.23, A_S8.23, A_S10.23, A_U8.9, A_U10.23, B_B12.18, B_F4.60, B_J18.11, B_L4.58
/SAB13: AP_R10.2, A_F9.13, A_L9.11, A_N8.2, A_N10.2, A_R8.2, A_S8.2, A_S10.2, A_U8.10, A_U10.2, B_B12.17, B_J7.13, B_J18.14, B_L4.57
/SAB14: AP_R10.26, A_L9.13, A_N8.26, A_N10.26, A_R8.26, A_S8.26, A_S10.26, B_J14.2, B_L4.56
/SCPUCLK: A_J8.15, A_L8.5
/SDB0: A_D9.13, A_H6.12, A_M9.18, A_N8.11, A_R8.11, A_S8.11, A_U8.11, B_J9.2, B_K13.13, B_K17.13, B_L9.2, B_M8.13, B_M10.13
/SDB1: A_D9.14, A_F6.2, A_M9.17, A_N8.12, A_R8.12, A_S8.12, A_U8.12, B_J9.3, B_K13.14, B_K17.14, B_L9.3, B_M8.14, B_M10.14
/SDB2: A_D9.15, A_G5.2, A_M9.16, A_N8.13, A_R8.13, A_S8.13, A_U8.13, B_J9.4, B_K13.15, B_K17.15, B_L9.4, B_M8.15, B_M10.15
/SDB3: A_D9.16, A_M9.15, A_N8.15, A_R8.15, A_S8.15, A_U8.15, B_J9.5, B_K13.16, B_K17.16, B_L9.5, B_M8.16, B_M10.16
/SDB4: A_D9.17, A_M9.14, A_N8.16, A_R8.16, A_S8.16, A_U8.16, B_J9.6, B_K13.17, B_K17.17, B_L9.6, B_M8.17, B_M10.17
/SDB5: A_D9.18, A_M9.13, A_N8.17, A_R8.17, A_S8.17, A_U8.17, B_J9.7, B_K13.18, B_K17.18, B_L9.7, B_M8.18, B_M10.18
/SDB6: A_D9.19, A_M9.12, A_N8.18, A_R8.18, A_S8.18, A_U8.18, B_J9.8, B_K13.19, B_K17.19, B_L9.8, B_M8.19, B_M10.19
/SDB7: A_D9.20, A_M9.11, A_N8.19, A_R8.19, A_S8.19, A_U8.19, B_J9.9, B_K13.20, B_K17.20, B_L9.9, B_M8.20, B_M10.20
/SDB8: AP_R10.11, A_H10.13, A_M10.18, A_N10.11, A_S10.11, A_U10.11, B_J8.2, B_K15.13, B_K18.13, B_L8.2, B_M6.13, B_M7.13
/SDB9: AP_R10.12, A_H10.14, A_M10.17, A_N10.12, A_S10.12, A_U10.12, B_J8.3, B_K15.14, B_K18.14, B_L8.3, B_M6.14, B_M7.14
/SDB10: AP_R10.13, A_H10.15, A_M10.16, A_N10.13, A_S10.13, A_U10.13, B_J8.4, B_K15.15, B_K18.15, B_L8.4, B_M6.15, B_M7.15
/SDB11: AP_R10.15, A_H10.16, A_M10.15, A_N10.15, A_S10.15, A_U10.15, B_J8.5, B_K15.16, B_K18.16, B_L8.5, B_M6.16, B_M7.16
/SDB12: AP_R10.16, A_H10.17, A_M10.14, A_N10.16, A_S10.16, A_U10.16, B_J8.6, B_K15.17, B_K18.17, B_L8.6, B_M6.17, B_M7.17
/SDB13: AP_R10.17, A_H10.18, A_M10.13, A_N10.17, A_S10.17, A_U10.17, B_J8.7, B_K15.18, B_K18.18, B_L8.7, B_M6.18, B_M7.18
/SDB14: AP_R10.18, A_H10.19, A_M10.12, A_N10.18, A_S10.18, A_U10.18, B_J8.8, B_K15.19, B_K18.19, B_L8.8, B_M6.19, B_M7.19
/SDB15: AP_R10.19, A_H10.20, A_M10.11, A_N10.19, A_S10.19, A_U10.19, B_J8.9, B_K15.20, B_K18.20, B_L8.9, B_M6.20, B_M7.20
/Shared Resources/A0: A_E9.12, A_E10.10, A_G10.10
/Shared Resources/A1: A_E10.9, A_G9.4, A_G10.9
/Shared Resources/A2: A_E10.8, A_G9.7, A_G10.8
/Shared Resources/A3: A_E10.7, A_G9.9, A_G10.7
/Shared Resources/A4: A_E10.6, A_G9.12, A_G10.6
/Shared Resources/A5: A_E10.5, A_G8.4, A_G10.5
/Shared Resources/A6: A_E10.4, A_G8.7, A_G10.4
/Shared Resources/A7: A_E10.3, A_G8.9, A_G10.3
/Shared Resources/A8: A_E10.25, A_G8.12, A_G10.25
/Shared Resources/A9: A_E10.24, A_F9.4, A_G10.24
/Shared Resources/A10: A_E10.21, A_F9.7, A_G10.21
/Shared Resources/A11: A_E10.23, A_F9.9, A_G10.23
/Shared Resources/A12: A_E10.2, A_F9.12, A_G10.2
/Shared Resources/ID0: A_D9.10, A_D10.10, A_E10.11
/Shared Resources/ID1: A_D9.9, A_D10.9, A_E10.12
/Shared Resources/ID2: A_D9.8, A_D10.8, A_E10.13
/Shared Resources/ID3: A_D9.7, A_D10.7, A_E10.15
/Shared Resources/ID4: A_D9.6, A_D10.6, A_E10.16
/Shared Resources/ID5: A_D9.5, A_D10.5, A_E10.17
/Shared Resources/ID6: A_D9.4, A_D10.4, A_E10.18
/Shared Resources/ID7: A_D9.3, A_D10.3, A_E10.19
/Shared Resources/ID8: A_G10.11, A_H9.10, A_H10.10
/Shared Resources/ID9: A_G10.12, A_H9.9, A_H10.9
/Shared Resources/ID10: A_G10.13, A_H9.8, A_H10.8
/Shared Resources/ID11: A_G10.15, A_H9.7, A_H10.7
/Shared Resources/ID12: A_G10.16, A_H9.6, A_H10.6
/Shared Resources/ID13: A_G10.17, A_H9.5, A_H10.5
/Shared Resources/ID14: A_G10.18, A_H9.4, A_H10.4
/Shared Resources/ID15: A_G10.19, A_H9.3, A_H10.3
/Shared Resources/SNMMPX: A_D10.12, A_E8.5, A_E9.1, A_F9.1, A_G5.9, A_G8.1, A_G9.1, A_H9.12
/Shared Resources/~CLWR: A_E8.18, A_E10.27
/Shared Resources/~CUWR: A_E8.19, A_G10.27
/Shared Resources/~MCOMRD: A_D10.21, A_E8.12, A_H9.21
/Shared Resources/~MWREN: A_D10.2, A_E8.15, A_H9.2
/Shared Resources/~SCOMRD: A_D9.21, A_E8.13, A_H10.21
/Shared Resources/~SNMMPX: A_D9.12, A_E8.3, A_G5.8, A_G5.12, A_H10.12
/Shared Resources/~SWREN: A_D9.2, A_E8.14, A_H10.2
/Slave CPU/A1: A_J8.29, A_L10.2
/Slave CPU/A2: A_J8.30, A_L10.4
/Slave CPU/A3: A_J8.31, A_L10.6
/Slave CPU/A4: A_J8.32, A_L10.8
/Slave CPU/A5: A_J8.33, A_L10.11
/Slave CPU/A6: A_J8.34, A_L10.13
/Slave CPU/A7: A_J8.35, A_L10.15
/Slave CPU/A8: A_J8.36, A_L10.17
/Slave CPU/A9: A_J8.37, A_L9.2
/Slave CPU/A10: A_J8.38, A_L9.4
/Slave CPU/A11: A_J8.39, A_L9.6
/Slave CPU/A12: A_J8.40, A_L9.10
/Slave CPU/A13: A_J8.41, A_L9.12
/Slave CPU/A14: A_J8.42, A_L9.14
/Slave CPU/D0: A_J8.5, A_M9.2
/Slave CPU/D1: A_J8.4, A_M9.3
/Slave CPU/D2: A_J8.3, A_M9.4
/Slave CPU/D3: A_J8.2, A_M9.5
/Slave CPU/D4: A_J8.1, A_M9.6
/Slave CPU/D5: A_J8.64, A_M9.7
/Slave CPU/D6: A_J8.63, A_M9.8
/Slave CPU/D7: A_J8.62, A_M9.9
/Slave CPU/D8: A_J8.61, A_M10.2
/Slave CPU/D9: A_J8.60, A_M10.3
/Slave CPU/D10: A_J8.59, A_M10.4
/Slave CPU/D11: A_J8.58, A_M10.5
/Slave CPU/D12: A_J8.57, A_M10.6
/Slave CPU/D13: A_J8.56, A_M10.7
/Slave CPU/D14: A_J8.55, A_M10.8
/Slave CPU/D15: A_J8.54, A_M10.9
/Slave CPU/SINT16EN: A_F6.5, A_H5.4
/Slave CPU/~SAS: A_F7.1, A_J8.6, A_K1.4, A_M8.5, A_T7.5
/Slave CPU/~SODTACK: A_S7.6, A_V10.9
/Slave CPU/~SSYSFLAG: A_F6.3, A_G5.3, A_H6.11, A_M8.10
/Slave CPU/~SWORKCS: A_M8.12, A_U8.20, A_U10.20
/Slave CPU/~VRAMDTACK: A_S7.12, A_V10.5
/Sound/A0: A_A3.4, A_A8.30, A_A10.10, A_B10.8, A_F7.11
/Sound/A1: A_A8.31, A_A10.9, A_B4.59, A_B10.7
/Sound/A2: A_A8.32, A_A10.8, A_B4.60, A_B10.6
/Sound/A3: A_A8.33, A_A10.7, A_B4.61, A_B10.5
/Sound/A4: A_A8.34, A_A10.6, A_B10.4
/Sound/A5: A_A8.35, A_A10.5, A_B10.3
/Sound/A6: A_A8.36, A_A10.4, A_B10.2
/Sound/A7: A_A8.37, A_A10.3, A_B10.1
/Sound/A8: A_A8.38, A_A10.25, A_B10.23
/Sound/A9: A_A8.39, A_A10.24, A_B10.22
/Sound/A10: A_A8.40, A_A10.21, A_B10.19
/Sound/A11: A_A8.1, A_A10.23
/Sound/A12: A_A8.2, A_A10.2, A_E7.1
/Sound/A13: A_A8.3, A_A10.26, A_E7.2
/Sound/A14: A_A8.4, A_A10.27, A_E7.3
/Sound/A15: A_A8.5, A_A10.20, A_E7.6
/Sound/D0: A_A3.10, A_A8.14, A_A10.19, A_B4.1, A_B7.3, A_B10.17, A_C10.2, A_D7.3, A_F8.12, A_U4.13
/Sound/D1: A_A3.12, A_A8.15, A_A10.18, A_B4.2, A_B7.4, A_B10.16, A_C10.5, A_D7.4, A_F8.2
/Sound/D2: A_A3.13, A_A8.12, A_A10.17, A_B4.3, A_B7.7, A_B10.15, A_C10.6, A_D7.7
/Sound/D3: A_A3.14, A_A8.8, A_A10.16, A_B4.4, A_B7.8, A_B10.14, A_C10.9, A_D7.8
/Sound/D4: A_A3.15, A_A8.7, A_A10.15, A_B4.5, A_B7.13, A_B10.13, A_C10.12, A_D7.13
/Sound/D5: A_A3.16, A_A8.9, A_A10.13, A_B4.6, A_B7.14, A_B10.11, A_C10.15, A_D7.14
/Sound/D6: A_A3.17, A_A8.10, A_A10.12, A_B4.7, A_B7.17, A_B10.10, A_C10.16, A_D7.17
/Sound/D7: A_A3.18, A_A8.13, A_A10.11, A_B4.8, A_B7.18, A_B10.9, A_C10.19, A_D7.18
/Sound/REF2V5: A_E3.5, A_E3.12, A_F3.3, A_F3.10
/Sound/SMPA0: A_A5.10, A_B4.33
/Sound/SMPA1: A_A5.9, A_B4.34
/Sound/SMPA2: A_A5.8, A_B4.36
/Sound/SMPA3: A_A5.7, A_B4.38
/Sound/SMPA4: A_A5.6, A_B4.39
/Sound/SMPA5: A_A5.5, A_B4.41
/Sound/SMPA6: A_A5.4, A_B4.43
/Sound/SMPA7: A_A5.3, A_B4.45
/Sound/SMPA8: A_A5.25, A_B4.44
/Sound/SMPA9: A_A5.24, A_B4.42
/Sound/SMPA10: A_A5.21, A_B4.35
/Sound/SMPA11: A_A5.23, A_B4.40
/Sound/SMPA12: A_A5.2, A_B4.47
/Sound/SMPA13: A_A5.26, A_B4.46
/Sound/SMPA14: A_A5.27, A_B4.49
/Sound/SMPA15: A_A5.1, A_B4.50
/Sound/SMPA16: A_A5.22, A_B4.37
/Sound/SMPD0: A_A5.11, A_B4.25
/Sound/SMPD1: A_A5.12, A_B4.27
/Sound/SMPD2: A_A5.13, A_B4.29
/Sound/SMPD3: A_A5.15, A_B4.31
/Sound/SMPD4: A_A5.16, A_B4.30
/Sound/SMPD5: A_A5.17, A_B4.28
/Sound/SMPD6: A_A5.18, A_B4.26
/Sound/SMPD7: A_A5.19, A_B4.24
/Sound/UPDA0: AP_C7.10, A_B8.26
/Sound/UPDA1: AP_C7.9, A_B8.27
/Sound/UPDA2: AP_C7.8, A_B8.28
/Sound/UPDA3: AP_C7.7, A_B8.29
/Sound/UPDA4: AP_C7.6, A_B8.30
/Sound/UPDA5: AP_C7.5, A_B8.31
/Sound/UPDA6: AP_C7.4, A_B8.32
/Sound/UPDA7: AP_C7.3, A_B8.33
/Sound/UPDA8: AP_C7.25, A_B8.34
/Sound/UPDD0: AP_C7.11, A_A7.3, A_B8.35
/Sound/UPDD1: AP_C7.12, A_A7.4, A_B8.36
/Sound/UPDD2: AP_C7.13, A_A7.7, A_B8.37
/Sound/UPDD3: AP_C7.15, A_A7.8, A_B8.38
/Sound/UPDD4: AP_C7.16, A_A7.13, A_B8.39
/Sound/UPDD5: AP_C7.17, A_A7.14, A_B8.1
/Sound/UPDD6: AP_C7.18, A_A7.17, A_B8.2
/Sound/UPDD7: AP_C7.19, A_A7.18, A_B8.3
/Sound/~BSY: A_E7.7, A_U4.15
/Sound/~DACS: A_B4.62, A_E7.12
/Sound/~MREQ: A_A8.19, A_E7.5
/Sound/~RD: A_A3.6, A_A8.21, A_A10.22, A_B10.20
/Sound/~RESET: A_E7.14, A_F8.3
/Sound/~RFSH: A_A8.28, A_F7.13
/Sound/~VDIN: A_B7.11, A_E7.10
/Sound/~VST: A_E7.9, A_F8.11
/Sound/~WR: A_A3.5, A_A8.22, A_B10.21
/Sprite Frame Buffers/C0: B_E22.2, B_E22.11, B_F12.83, B_H22.2, B_H22.11
/Sprite Frame Buffers/C1: B_E22.4, B_E22.13, B_F12.82, B_H22.4, B_H22.13
/Sprite Frame Buffers/C2: B_E22.6, B_E22.15, B_F12.81, B_H22.6, B_H22.15
/Sprite Frame Buffers/C3: B_E22.8, B_E22.17, B_F12.80, B_H22.8, B_H22.17
/Sprite Frame Buffers/CX0: B_E23.2, B_E23.11, B_F12.2, B_H23.2, B_H23.11
/Sprite Frame Buffers/CX1: B_E23.4, B_E23.13, B_F12.3, B_H23.4, B_H23.13
/Sprite Frame Buffers/CX2: B_E23.6, B_E23.15, B_F12.4, B_H23.6, B_H23.15
/Sprite Frame Buffers/CX3: B_E23.8, B_E23.17, B_F12.5, B_H23.8, B_H23.17
/Sprite Frame Buffers/FA0: B_A17.14, B_B16.14, B_C16.15
/Sprite Frame Buffers/FA1: B_A17.13, B_B16.13, B_C16.14
/Sprite Frame Buffers/FA2: B_A17.12, B_B16.12, B_C16.13
/Sprite Frame Buffers/FA3: B_A17.11, B_B16.11, B_C16.12
/Sprite Frame Buffers/FA4: B_A17.8, B_B16.8, B_C16.11
/Sprite Frame Buffers/FA5: B_A17.7, B_B16.7, B_C16.10
/Sprite Frame Buffers/FA6: B_A17.6, B_B16.6, B_C16.9
/Sprite Frame Buffers/FA7: B_A17.10, B_B16.10, B_C16.8
/Sprite Frame Buffers/FA20: B_E16.14, B_E17.14, B_F16.15
/Sprite Frame Buffers/FA21: B_E16.13, B_E17.13, B_F16.14
/Sprite Frame Buffers/FA22: B_E16.12, B_E17.12, B_F16.13
/Sprite Frame Buffers/FA23: B_E16.11, B_E17.11, B_F16.12
/Sprite Frame Buffers/FA24: B_E16.8, B_E17.8, B_F16.11
/Sprite Frame Buffers/FA25: B_E16.7, B_E17.7, B_F16.10
/Sprite Frame Buffers/FA26: B_E16.6, B_E17.6, B_F16.9
/Sprite Frame Buffers/FA27: B_E16.10, B_E17.10, B_F16.8
/Sprite Frame Buffers/FB0: B_A19.10, B_B19.10, B_C16.25
/Sprite Frame Buffers/FB1: B_A19.6, B_B19.6, B_C16.24
/Sprite Frame Buffers/FB2: B_A19.7, B_B19.7, B_C16.23
/Sprite Frame Buffers/FB3: B_A19.8, B_B19.8, B_C16.22
/Sprite Frame Buffers/FB4: B_A19.11, B_B19.11, B_C16.21
/Sprite Frame Buffers/FB5: B_A19.12, B_B19.12, B_C16.20
/Sprite Frame Buffers/FB6: B_A19.13, B_B19.13, B_C16.19
/Sprite Frame Buffers/FB7: B_A19.14, B_B19.14, B_C16.18
/Sprite Frame Buffers/FB20: B_E18.14, B_E19.14, B_F16.25
/Sprite Frame Buffers/FB21: B_E18.13, B_E19.13, B_F16.24
/Sprite Frame Buffers/FB22: B_E18.12, B_E19.12, B_F16.23
/Sprite Frame Buffers/FB23: B_E18.11, B_E19.11, B_F16.22
/Sprite Frame Buffers/FB24: B_E18.8, B_E19.8, B_F16.21
/Sprite Frame Buffers/FB25: B_E18.7, B_E19.7, B_F16.20
/Sprite Frame Buffers/FB26: B_E18.6, B_E19.6, B_F16.19
/Sprite Frame Buffers/FB27: B_E18.10, B_E19.10, B_F16.18
/Sprite Frame Buffers/FC0: B_C16.50, B_D16.14, B_D17.14
/Sprite Frame Buffers/FC1: B_C16.51, B_D16.13, B_D17.13
/Sprite Frame Buffers/FC2: B_C16.52, B_D16.12, B_D17.12
/Sprite Frame Buffers/FC3: B_C16.53, B_D16.11, B_D17.11
/Sprite Frame Buffers/FC4: B_C16.54, B_D16.8, B_D17.8
/Sprite Frame Buffers/FC5: B_C16.55, B_D16.7, B_D17.7
/Sprite Frame Buffers/FC6: B_C16.56, B_D16.6, B_D17.6
/Sprite Frame Buffers/FC7: B_C16.57, B_D16.10, B_D17.10
/Sprite Frame Buffers/FC20: B_F16.50, B_H16.14, B_H17.14
/Sprite Frame Buffers/FC21: B_F16.51, B_H16.13, B_H17.13
/Sprite Frame Buffers/FC22: B_F16.52, B_H16.12, B_H17.12
/Sprite Frame Buffers/FC23: B_F16.53, B_H16.11, B_H17.11
/Sprite Frame Buffers/FC24: B_F16.54, B_H16.8, B_H17.8
/Sprite Frame Buffers/FC25: B_F16.55, B_H16.7, B_H17.7
/Sprite Frame Buffers/FC26: B_F16.56, B_H16.6, B_H17.6
/Sprite Frame Buffers/FC27: B_F16.57, B_H16.10, B_H17.10
/Sprite Frame Buffers/FD0: B_C16.40, B_D18.10, B_D19.10
/Sprite Frame Buffers/FD1: B_C16.41, B_D18.6, B_D19.6
/Sprite Frame Buffers/FD2: B_C16.42, B_D18.7, B_D19.7
/Sprite Frame Buffers/FD3: B_C16.43, B_D18.8, B_D19.8
/Sprite Frame Buffers/FD4: B_C16.44, B_D18.11, B_D19.11
/Sprite Frame Buffers/FD5: B_C16.45, B_D18.12, B_D19.12
/Sprite Frame Buffers/FD6: B_C16.46, B_D18.13, B_D19.13
/Sprite Frame Buffers/FD7: B_C16.47, B_D18.14, B_D19.14
/Sprite Frame Buffers/FD20: B_F16.40, B_H18.14, B_H19.14
/Sprite Frame Buffers/FD21: B_F16.41, B_H18.13, B_H19.13
/Sprite Frame Buffers/FD22: B_F16.42, B_H18.12, B_H19.12
/Sprite Frame Buffers/FD23: B_F16.43, B_H18.11, B_H19.11
/Sprite Frame Buffers/FD24: B_F16.44, B_H18.8, B_H19.8
/Sprite Frame Buffers/FD25: B_F16.45, B_H18.7, B_H19.7
/Sprite Frame Buffers/FD26: B_F16.46, B_H18.6, B_H19.6
/Sprite Frame Buffers/FD27: B_F16.47, B_H18.10, B_H19.10
/Sprite Frame Buffers/HD2: B_C16.3, B_F12.28, B_F16.3
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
